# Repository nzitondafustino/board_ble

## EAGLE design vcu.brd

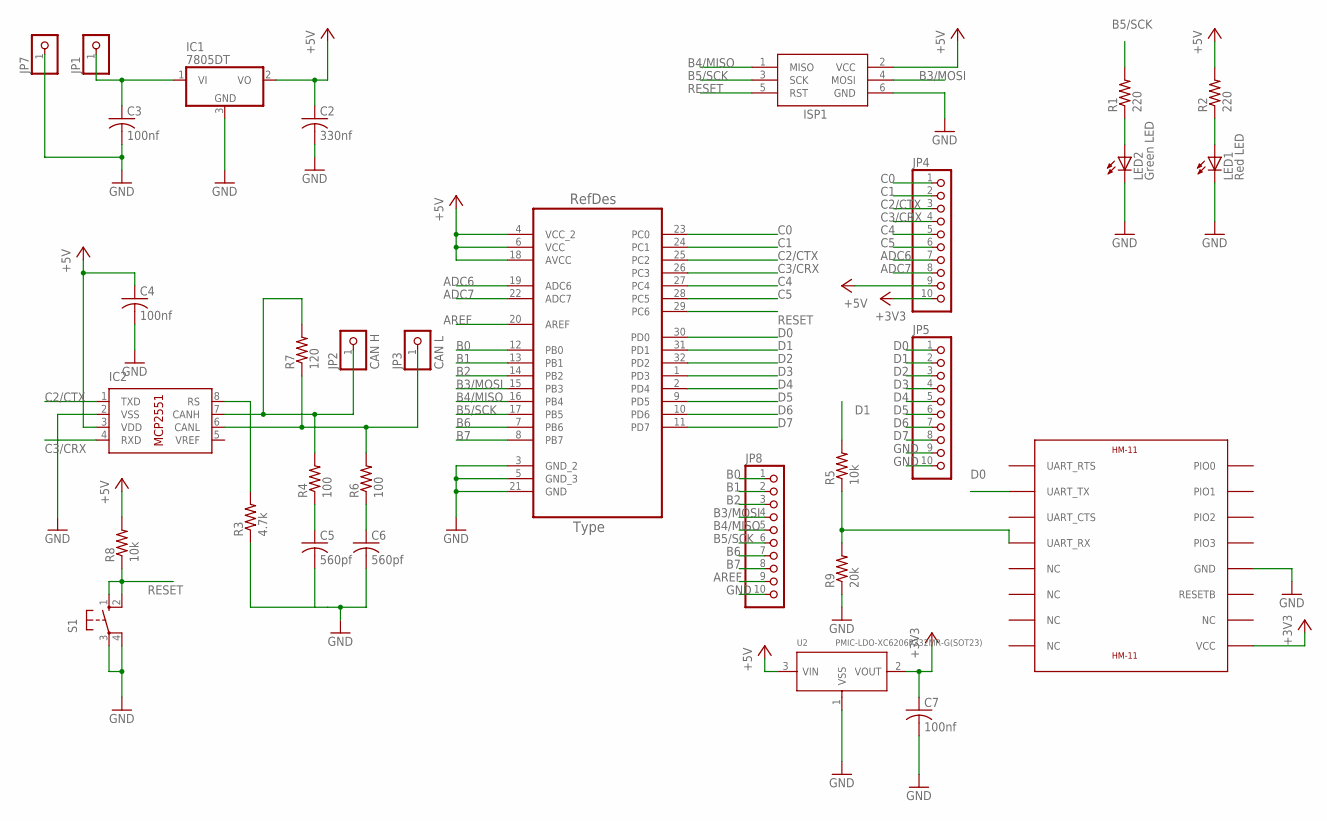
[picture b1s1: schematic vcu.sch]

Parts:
C2: 330nf; C0402
C3, C4, C7: 100nf; C0402
C5, C6: 560pf; C0402
IC1: 7805DT; TO252
IC2: MCP2551/SN; SO08
ISP1: AVRISP-6; AVRISP
JP1, JP7: PINHD-1X1CB; 1X01-CLEANBIG
JP2: CAN H; 1X01-CLEANBIG
JP3: CAN L; 1X01-CLEANBIG
JP4, JP5, JP8: PINHD-1X10; 1X10
LED1: Red LED; LED-0603
LED2: Green LED; LED-0603
R1, R2: 220; M0805
R3: 4.7k; M0805
R4, R6: 100; M0805
R5, R8: 10k; M0805
R7: 120; M0805
R9: 20k; M0805
S1: 10-XX; B3F-10XX
U1: ATMEGA328P-AU; QFP80P900X900X120-32N
U2: PMIC-LDO-XC6206P332MR-G(SOT23); SOT-23
U$1: HM-11

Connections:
+3V3: C7.1, JP4.10, U2.2 (VOUT), U$1.VCC
+5V: C2.1, C4.1, IC1.2 (VO), IC2.3 (VDD), ISP1.2 (VCC), JP4.9, R2.2, R8.2, U1.4 (VCC_2), U1.6 (VCC), U1.18 (AVCC), U2.3 (VIN)
ADC6: JP4.7, U1.19 (ADC6)
ADC7: JP4.8, U1.22 (ADC7)
AREF: JP8.9, U1.20 (AREF)
B0: JP8.1, U1.12 (PB0)
B1: JP8.2, U1.13 (PB1)
B2: JP8.3, U1.14 (PB2)
B3/MOSI: ISP1.4 (MOSI), JP8.4, U1.15 (PB3)
B4/MISO: ISP1.1 (MISO), JP8.5, U1.16 (PB4)
B5/SCK: ISP1.3 (SCK), JP8.6, R1.2, U1.17 (PB5)
B6: JP8.7, U1.7 (PB6)
B7: JP8.8, U1.8 (PB7)
C0: JP4.1, U1.23 (PC0)
C1: JP4.2, U1.24 (PC1)
C2/CTX: IC2.1 (TXD), JP4.3, U1.25 (PC2)
C3/CRX: IC2.4 (RXD), JP4.4, U1.26 (PC3)
C4: JP4.5, U1.27 (PC4)
C5: JP4.6, U1.28 (PC5)
D0: JP5.1, U1.30 (PD0), U$1.UART_TX
D1: JP5.2, R5.2, U1.31 (PD1)
D2: JP5.3, U1.32 (PD2)
D3: JP5.4, U1.1 (PD3)
D4: JP5.5, U1.2 (PD4)
D5: JP5.6, U1.9 (PD5)
D6: JP5.7, U1.10 (PD6)
D7: JP5.8, U1.11 (PD7)
unnamed: C3.1, IC1.1 (VI), JP1.1
unnamed: R5.1, R9.2, U$1.UART_RX
unnamed: LED1.A, R2.1
unnamed: LED2.A, R1.1
unnamed: IC2.7 (CANH), JP2.1, R4.2, R7.2
unnamed: IC2.6 (CANL), JP3.1, R6.2, R7.1
unnamed: C6.1, R6.1
unnamed: C5.1, R4.1
unnamed: IC2.8 (RS), R3.2
RESET: ISP1.5 (RST), R8.1, S1.1 (S), S1.2 (S1), U1.29 (PC6)

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
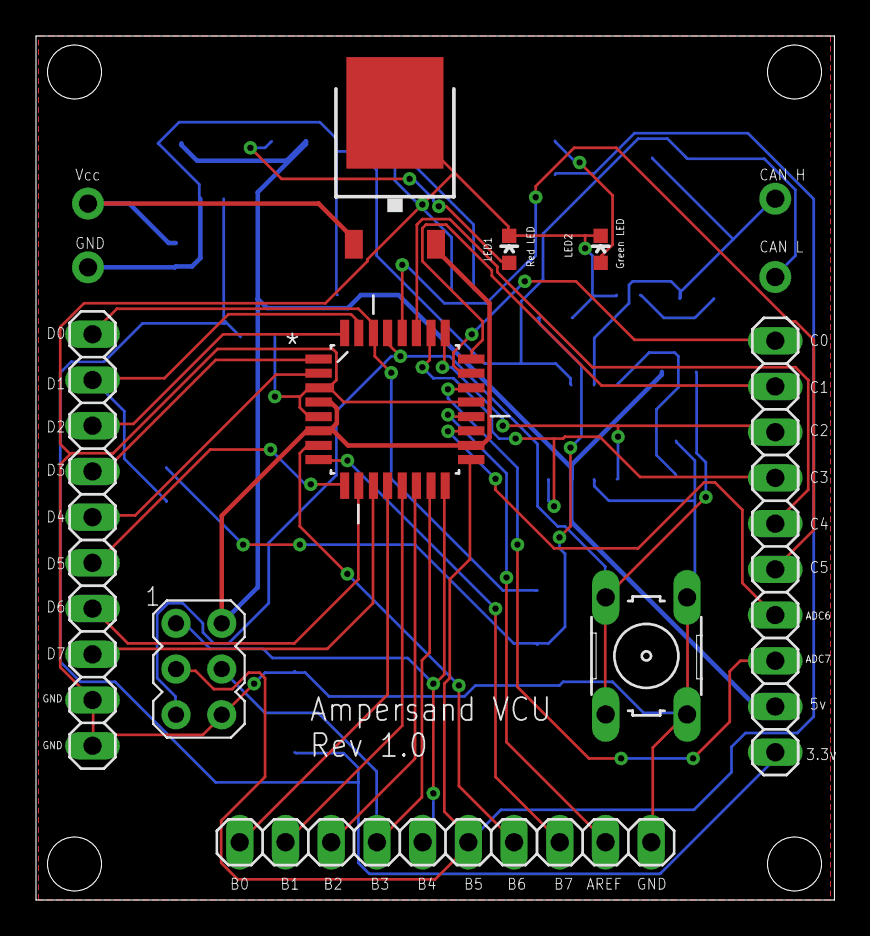
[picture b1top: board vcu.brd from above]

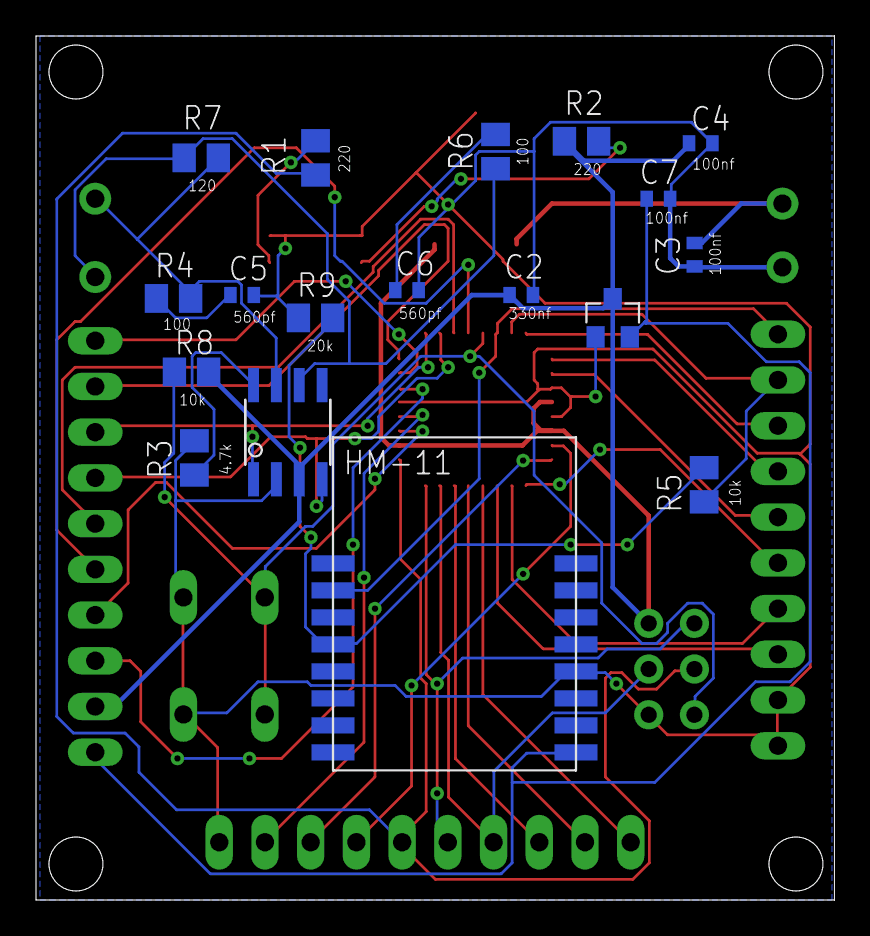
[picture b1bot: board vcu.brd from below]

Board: 2 copper layers, 44.4 x 48.0 mm, 31 parts (18 on the bottom side), 38 nets.

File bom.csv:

Qty,Designator,Footprint,Comment,LCSC Part #
,C2,C0402,330nf 16v,
3,"C3,C4,C7",C0402,100nf 16v,
2,"C5,C6",C0402,560pf 16v,
1,IC1,TO252,7805DT 1A,
1,IC2,SO08,MCP2551/SN,
1,ISP1,AVRISP,AVRISP-6,
1,LED1,LED-0603,Red LED,
1,LED2,LED-0603,Green LED,
2,"R1,R2",M0805,220,
1,R3,M0805,4.7k,
2,"R4,R6",M0805,100,
2,"R5,R8",M0805,10k,
1,R7,M0805,120,
1,R9,M0805,20k,
1,S1,B3F-10XX,,
1,Hm-11,HM-11,HM-11 BLE module,
1,U1,QFP80P900X900X120-32N,ATMEGA328P-AU, C14877
1,U2,SOT-23,PMIC-LDO-XC6206P332MR-G(SOT23),

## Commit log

2019-12-29 improved vcu with ble 4.0
2019-12-29 vcu with ble
2020-01-17 improvement

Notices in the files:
parts and their libraries:
SparkFun: Licensing: CC v3.0 Share-Alike You are welcome to use this library for commercial purposes.
